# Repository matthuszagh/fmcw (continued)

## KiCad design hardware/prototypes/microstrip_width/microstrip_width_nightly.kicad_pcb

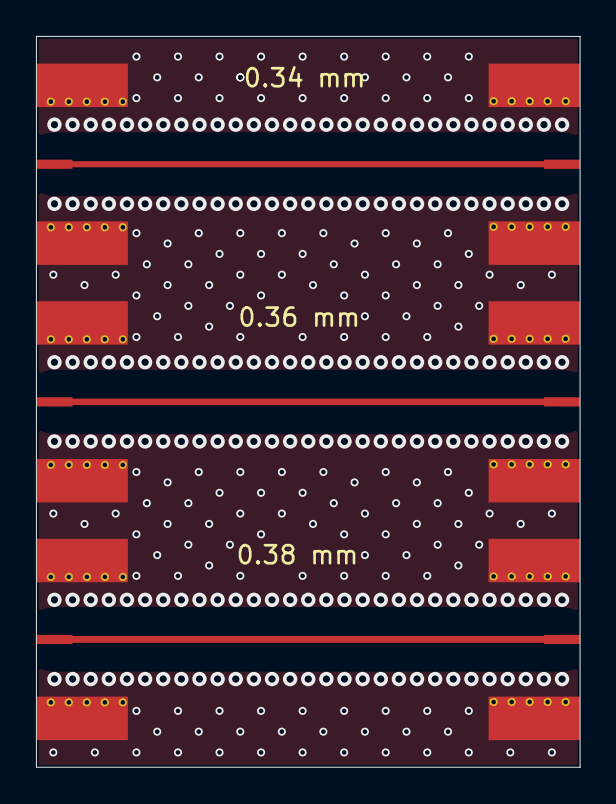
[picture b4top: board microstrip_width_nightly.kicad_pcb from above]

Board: 4 copper layers, 30.2 x 40.6 mm, 6 parts (0 on the bottom side), 4 nets.

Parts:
J1, J2, J3, J4, J5, J6: Conn_Coaxial; BU-1420701851_SMA

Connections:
GND: J1.2 (Ext), J2.2 (Ext), J3.2 (Ext), J4.2 (Ext), J5.2 (Ext), J6.2 (Ext)
unnamed: J1.1 (In), J4.1 (In)
unnamed: J2.1 (In), J5.1 (In)
unnamed: J3.1 (In), J6.1 (In)
